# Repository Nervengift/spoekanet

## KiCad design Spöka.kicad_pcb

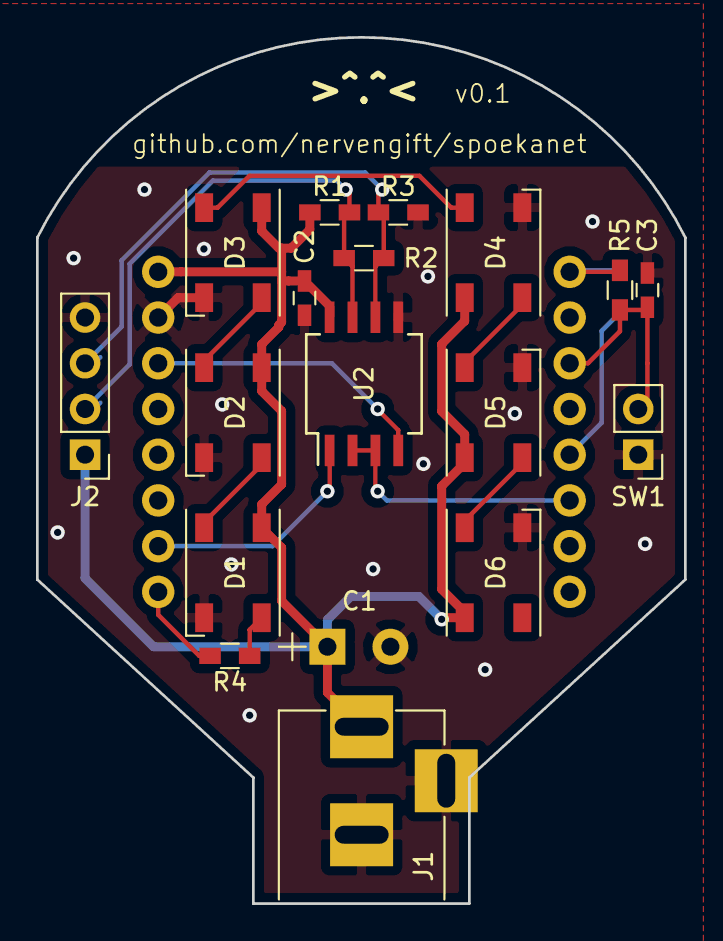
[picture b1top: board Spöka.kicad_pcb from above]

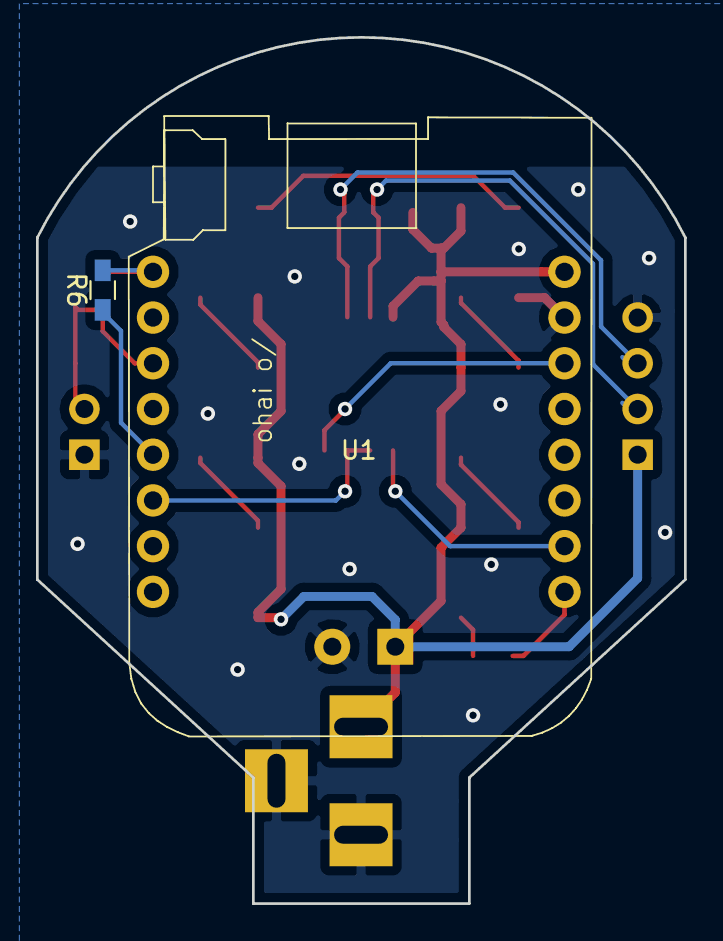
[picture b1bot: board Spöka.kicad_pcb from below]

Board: 2 copper layers, 36.0 x 48.1 mm, 20 parts (2 on the bottom side), 17 nets.

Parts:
C1: 1000u; CP_Radial_D10.0mm_P3.50mm
C2, C3: 100n; C_0603_HandSoldering
D1, D2, D3, D4, D5, D6: WS2812B; LED_WS2812B-PLCC4
J1: Barrel_Jack; BARREL_JACK
J2: DMX_header; Pin_Header_Straight_1x04_Pitch2.54mm
R1, R3, R4: 560; R_0603_HandSoldering
R2: 130; R_0603_HandSoldering
R5, R6: 10k; R_0603_HandSoldering
SW1: SW_Push; Pin_Header_Straight_1x02_Pitch2.54mm
U1: WeMos_mini; D1_mini_board
U2: MAX485E; SO-8_5.3x6.2mm_Pitch1.27mm

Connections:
+3V3: R5.1, R6.2, U1.16
DIR_B: U1.11, U2.2, U2.3
GND: C1.2, C2.2, C3.1, D1.3, D2.3, D3.3, D4.3, D5.3, D6.3, J1.2, J1.3, J2.4, R3.2, SW1.1, U1.2, U2.5
unnamed: C3.2, R5.2, SW1.2, U1.14
unnamed: D1.2, D2.4
unnamed: D1.4, R4.1
unnamed: D2.2, D3.4
unnamed: D3.2, D4.4
unnamed: D4.2, D5.4
unnamed: D5.2, D6.4
unnamed: J2.2, R1.2, R2.1, U2.7
unnamed: J2.3, R2.2, R3.1, U2.6
unnamed: R6.1, U1.12
RX: U1.7, U2.1
TX_A: R4.2, U1.8
TX_B: U1.3, U2.4
VCC: C1.1, C2.1, D1.1, D2.1, D3.1, D4.1, D5.1, D6.1, J1.1, J2.1, R1.1, U1.1, U2.8

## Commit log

2018-07-11 Initial commit, v0.1
